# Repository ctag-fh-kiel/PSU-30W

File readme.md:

# Eurorack power supply unit 30W with DCDC converter
- Uses 9-12V 3A power adaptor (e.g. from LED power supply)
- Converts +12V in to +/- 12V and +5V out
- Can be used fully isolated

# Includes 3D PLA printed housing
- Use Eurorack_Case_3D_Print_PLA_gcode.zip directly in your 3D printer (attention, veeeery long print duration), tested on Prusa i3

# Includes lasercut case (85hp) with lid
- created using https://www.festi.info/boxes.py/ and https://inkscape.org/
- Material: 4mm thick wood or PMMA (70 x 46 cm)
- Module support rails: APRA 241 (85hp)

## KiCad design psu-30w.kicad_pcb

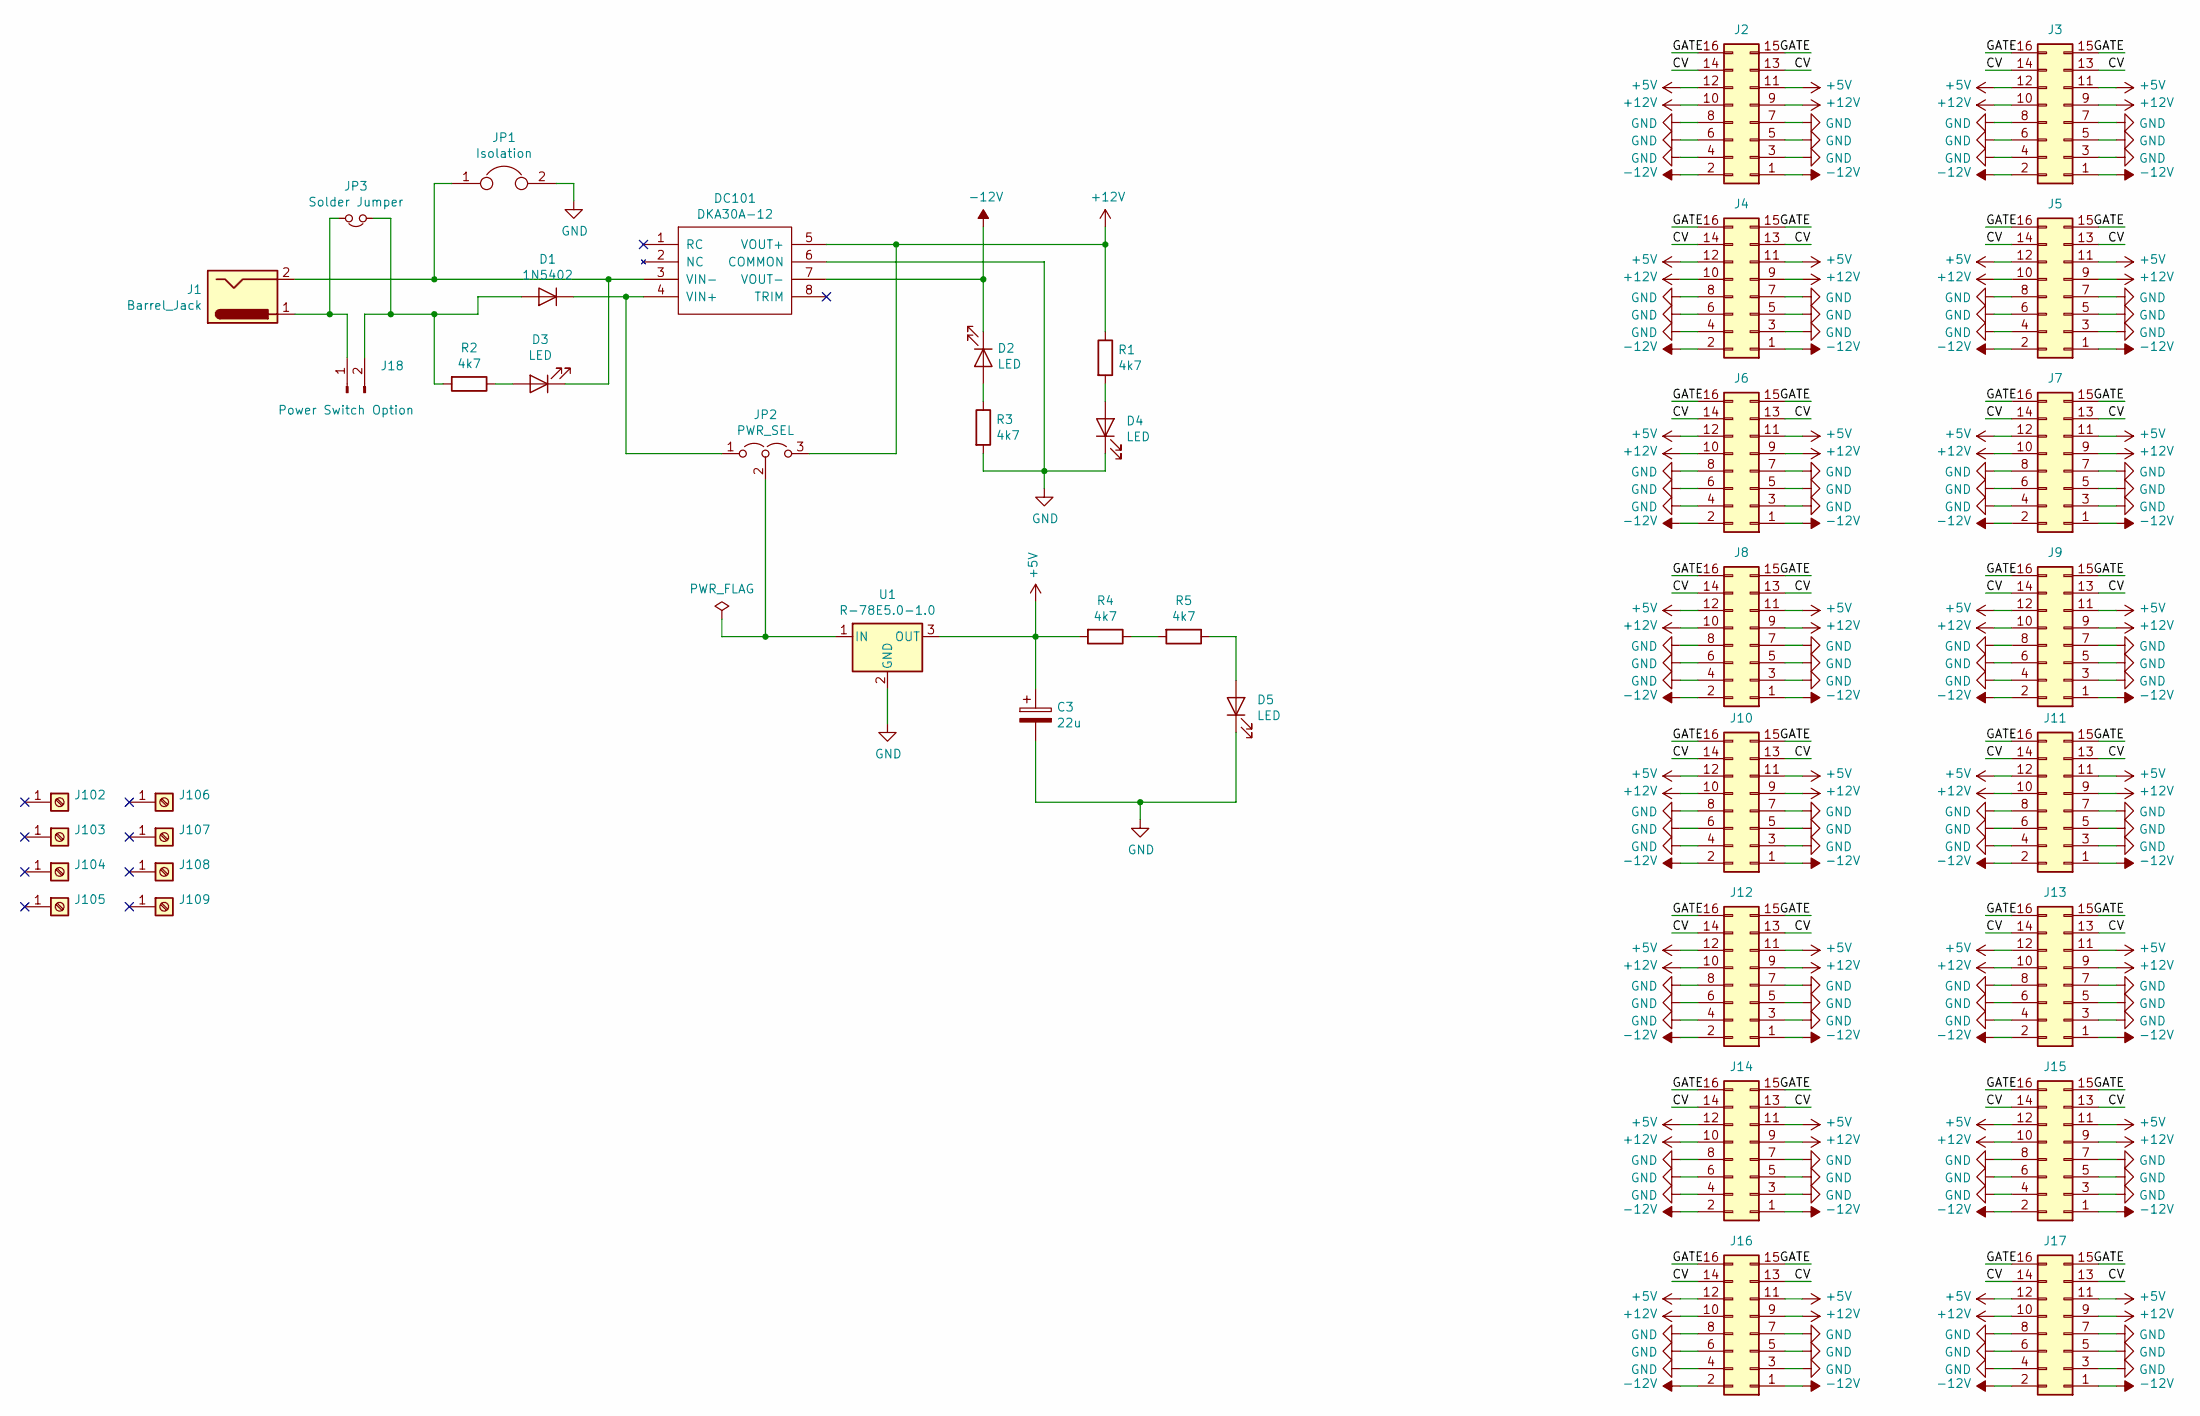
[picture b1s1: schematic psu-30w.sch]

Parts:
C3: 22u; CP_Elec_10x10
D1: 1N5402; D_DO-201AD_P15.24mm_Horizontal
D2, D3, D4, D5: LED; LED_D5.0mm
DC101: DKA30A-12
J1: Barrel_Jack; PJ-059A
J2, J3, J4, J5, J6, J7, J8, J9, J10, J11, J12, J13, J14, J15, J16, J17: PinHeader_2x08_P2.54mm_Vertical
J18: Power Switch Option; PinHeader_1x02_P2.54mm_Vertical
J102, J103, J104, J105, J106, J107, J108, J109: MountingHole_3.2mm_M3_DIN965_Pad
JP1: Isolation; PinHeader_1x02_P2.54mm_Vertical
JP2: PWR_SEL; PinHeader_1x03_P2.54mm_Vertical
JP3: Solder Jumper; SolderJumper-2_P1.3mm_Open_TrianglePad1.0x1.5mm
R1, R2, R3, R4, R5: 4k7; R_0805_2012Metric_Pad1.15x1.40mm_HandSolder
U1: R-78E5.0-1.0; SIP3_11.6x8.5mm

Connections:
+5V: C3.1, J2.11, J2.12, J3.11, J3.12, J4.11, J4.12, J5.11, J5.12, J6.11, J6.12, J7.11, J7.12, J8.11, J8.12, J9.11, J9.12, J10.11, J10.12, J11.11, J11.12, J12.11, J12.12, J13.11, J13.12, J14.11, J14.12, J15.11, J15.12, J16.11, J16.12, J17.11, J17.12, R4.2, U1.3 (OUT)
+12V: DC101.5 (VOUT+), J2.9, J2.10, J3.9, J3.10, J4.9, J4.10, J5.9, J5.10, J6.9, J6.10, J7.9, J7.10, J8.9, J8.10, J9.9, J9.10, J10.9, J10.10, J11.9, J11.10, J12.9, J12.10, J13.9, J13.10, J14.9, J14.10, J15.9, J15.10, J16.9, J16.10, J17.9, J17.10, JP2.3 (B), R1.1
-12V: D2.1 (K), DC101.7 (VOUT-), J2.1, J2.2, J3.1, J3.2, J4.1, J4.2, J5.1, J5.2, J6.1, J6.2, J7.1, J7.2, J8.1, J8.2, J9.1, J9.2, J10.1, J10.2, J11.1, J11.2, J12.1, J12.2, J13.1, J13.2, J14.1, J14.2, J15.1, J15.2, J16.1, J16.2, J17.1, J17.2
/CV: J2.13, J2.14, J3.13, J3.14, J4.13, J4.14, J5.13, J5.14, J6.13, J6.14, J7.13, J7.14, J8.13, J8.14, J9.13, J9.14, J10.13, J10.14, J11.13, J11.14, J12.13, J12.14, J13.13, J13.14, J14.13, J14.14, J15.13, J15.14, J16.13, J16.14, J17.13, J17.14
/GATE: J2.15, J2.16, J3.15, J3.16, J4.15, J4.16, J5.15, J5.16, J6.15, J6.16, J7.15, J7.16, J8.15, J8.16, J9.15, J9.16, J10.15, J10.16, J11.15, J11.16, J12.15, J12.16, J13.15, J13.16, J14.15, J14.16, J15.15, J15.16, J16.15, J16.16, J17.15, J17.16
GND: C3.2, D4.1 (K), D5.1 (K), DC101.6 (COMMON), J2.3, J2.4, J2.5, J2.6, J2.7, J2.8, J3.3, J3.4, J3.5, J3.6, J3.7, J3.8, J4.3, J4.4, J4.5, J4.6, J4.7, J4.8, J5.3, J5.4, J5.5, J5.6, J5.7, J5.8, J6.3, J6.4, J6.5, J6.6, J6.7, J6.8, J7.3, J7.4, J7.5, J7.6, J7.7, J7.8, J8.3, J8.4, J8.5, J8.6, J8.7, J8.8, J9.3, J9.4, J9.5, J9.6, J9.7, J9.8, J10.3, J10.4, J10.5, J10.6, J10.7, J10.8, J11.3, J11.4, J11.5, J11.6, J11.7, J11.8, J12.3, J12.4, J12.5, J12.6, J12.7, J12.8, J13.3, J13.4, J13.5, J13.6, J13.7, J13.8, J14.3, J14.4, J14.5, J14.6, J14.7, J14.8, J15.3, J15.4, J15.5, J15.6, J15.7, J15.8, J16.3, J16.4, J16.5, J16.6, J16.7, J16.8, J17.3, J17.4, J17.5, J17.6, J17.7, J17.8, JP1.2, R3.2, U1.2 (GND)
unnamed: D1.1 (K), DC101.4 (VIN+), JP2.1 (A)
unnamed: D1.2 (A), J18.2, JP3.1, R2.2
unnamed: D2.2 (A), R3.1
unnamed: D3.1 (K), DC101.3 (VIN-), J1.2, JP1.1
unnamed: D3.2 (A), R2.1
unnamed: D4.2 (A), R1.2
unnamed: D5.2 (A), R5.1
unnamed: J1.1, J18.1, JP3.2
unnamed: JP2.2 (C), U1.1 (IN)
unnamed: R4.1, R5.2

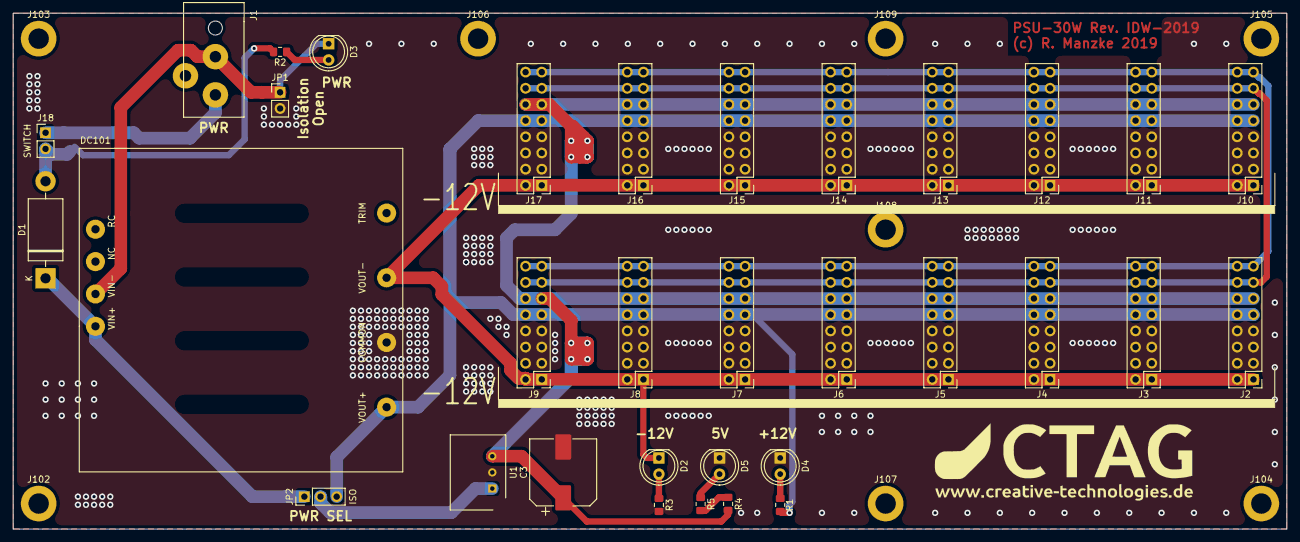
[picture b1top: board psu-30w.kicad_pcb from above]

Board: 2 copper layers, 200.0 x 81.0 mm, 42 parts (1 on the bottom side), 16 nets.

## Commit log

2019-04-02 initial
2019-04-03 Gerbers
2019-04-05 production files rev b
2019-09-09 added readme and bom
2019-10-15 adaptations + simplifications
2019-10-17 order version
2021-08-02 schematic pdf
2021-12-07 Create LICENSE
2021-12-07 directory cleaned up
2021-12-07 files
2021-12-15 .stl file for housing added...
2021-12-20 added files for lasercut case
2022-05-11 added interactive BOM
